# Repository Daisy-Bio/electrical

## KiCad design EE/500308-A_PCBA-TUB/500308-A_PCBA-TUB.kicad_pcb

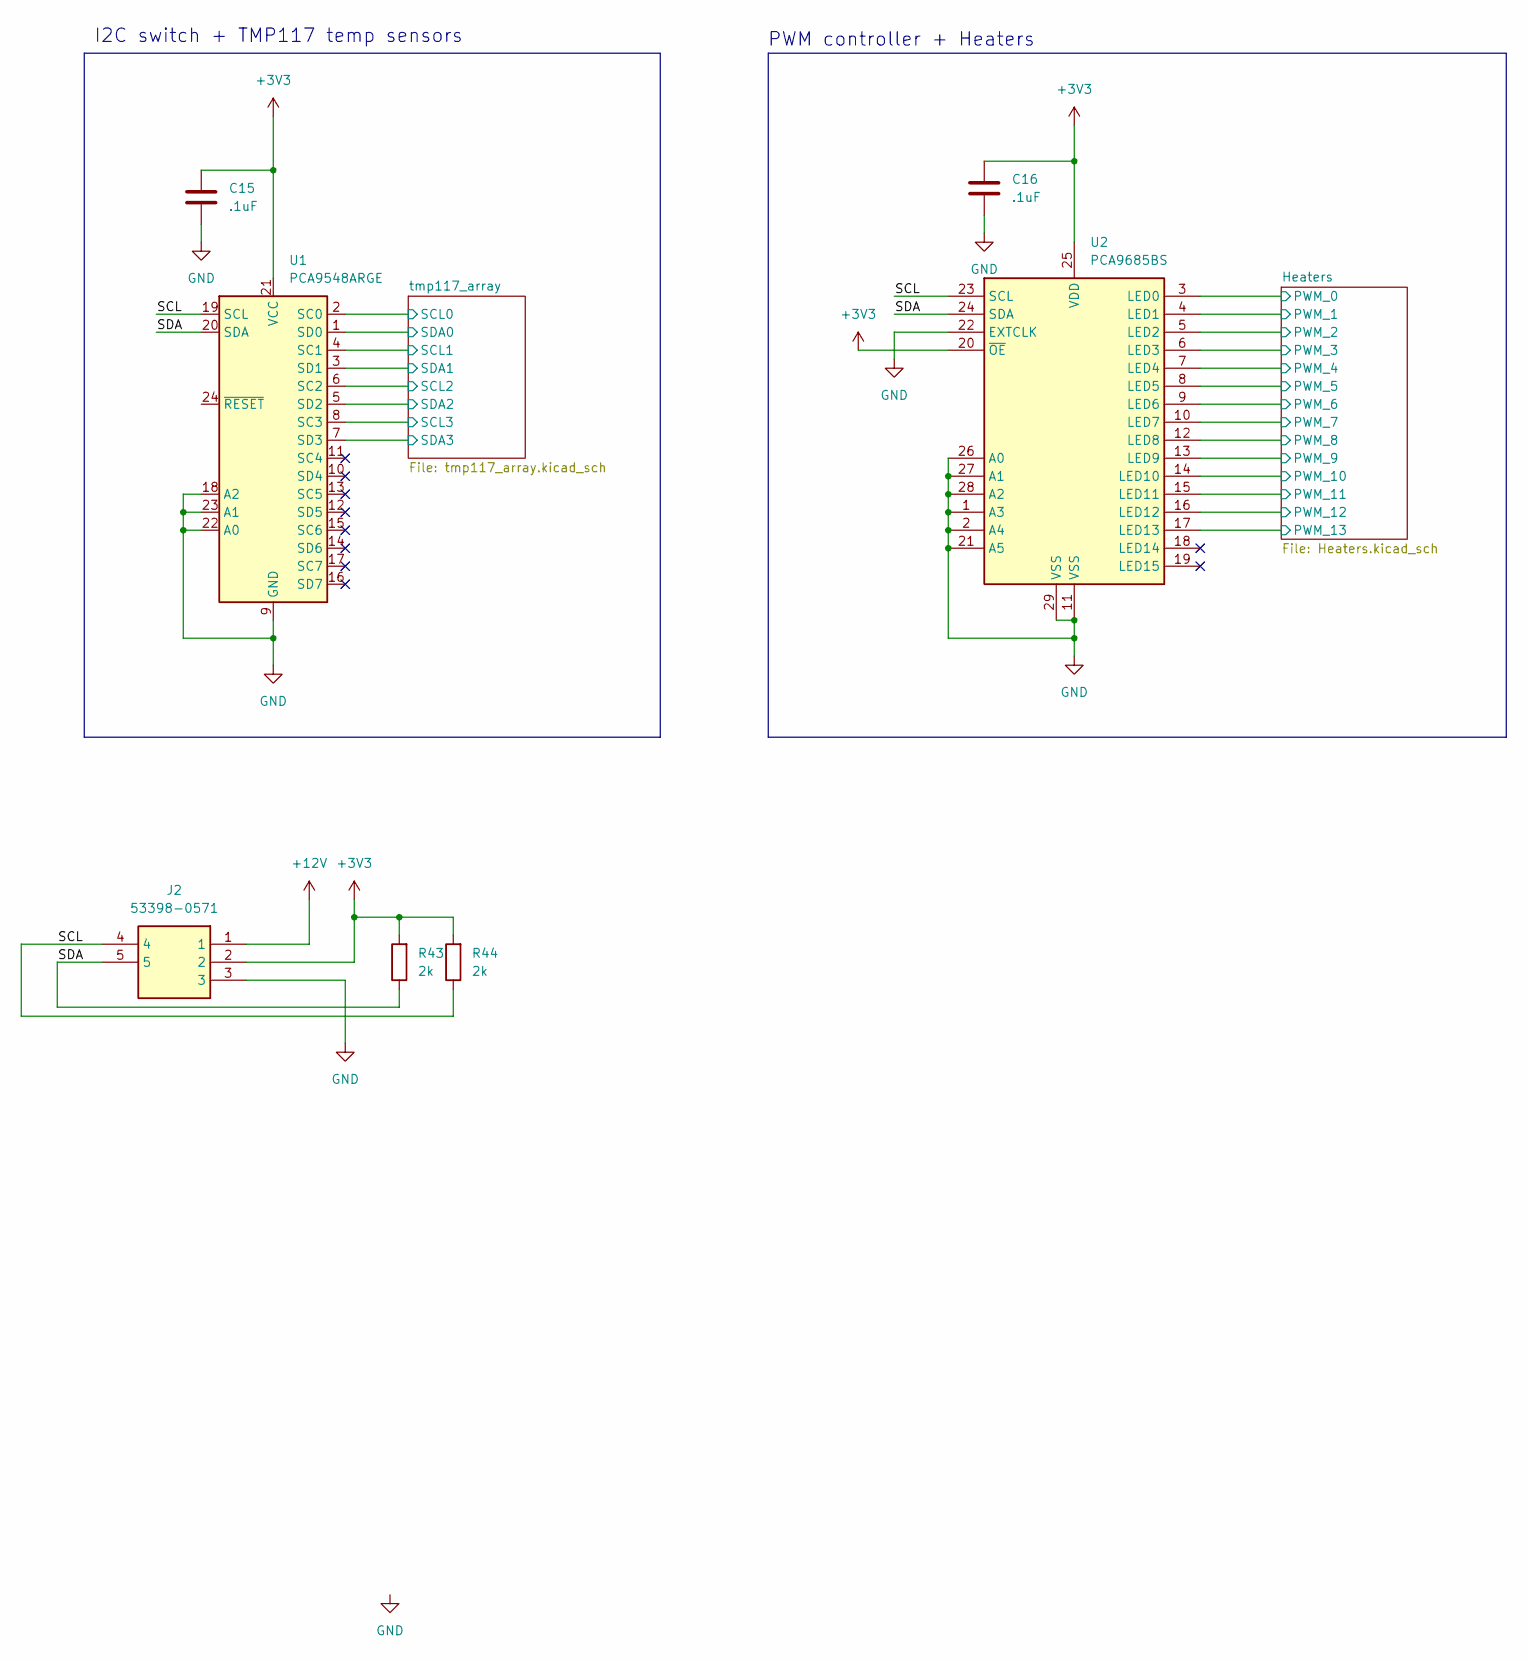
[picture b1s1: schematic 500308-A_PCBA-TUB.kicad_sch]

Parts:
C15, C16: .1uF; C_0402_1005Metric_Pad0.74x0.62mm_HandSolder
J2: 53398-0571; Mouser Part Number 538-53398-0571
R43, R44: 2k; R_0402_1005Metric
U1: PCA9548ARGE; Texas_RGE0024C_VQFN-24-1EP_4x4mm_P0.5mm_EP2.1x2.1mm
U2: PCA9685BS; QFN-28-1EP_6x6mm_P0.65mm_EP4.25x4.25mm

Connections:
+3V3: C15.1, C16.1, J2.2, R43.2, R44.2, U1.21 (VCC), U2.20 (~OE), U2.25 (VDD); also elsewhere on the board
+12V: J2.1; also elsewhere on the board
/Heaters/PWM_0: U2.3 (LED0); also elsewhere on the board
/Heaters/PWM_1: U2.4 (LED1); also elsewhere on the board
/Heaters/PWM_2: U2.5 (LED2); also elsewhere on the board
/Heaters/PWM_3: U2.6 (LED3); also elsewhere on the board
/Heaters/PWM_4: U2.7 (LED4); also elsewhere on the board
/Heaters/PWM_5: U2.8 (LED5); also elsewhere on the board
/Heaters/PWM_6: U2.9 (LED6); also elsewhere on the board
/Heaters/PWM_7: U2.10 (LED7); also elsewhere on the board
/Heaters/PWM_8: U2.12 (LED8); also elsewhere on the board
/Heaters/PWM_9: U2.13 (LED9); also elsewhere on the board
/Heaters/PWM_10: U2.14 (LED10); also elsewhere on the board
/Heaters/PWM_11: U2.15 (LED11); also elsewhere on the board
/Heaters/PWM_12: U2.16 (LED12); also elsewhere on the board
/Heaters/PWM_13: U2.17 (LED13); also elsewhere on the board
/SCL: J2.4, R44.1, U1.19 (SCL), U2.23 (SCL)
/SDA: J2.5, R43.1, U1.20 (SDA), U2.24 (SDA)
/tmp117_array/SCL0: U1.2 (SC0); also elsewhere on the board
/tmp117_array/SCL1: U1.4 (SC1); also elsewhere on the board
/tmp117_array/SCL2: U1.6 (SC2); also elsewhere on the board
/tmp117_array/SCL3: U1.8 (SC3); also elsewhere on the board
/tmp117_array/SDA0: U1.1 (SD0); also elsewhere on the board
/tmp117_array/SDA1: U1.3 (SD1); also elsewhere on the board
/tmp117_array/SDA2: U1.5 (SD2); also elsewhere on the board
/tmp117_array/SDA3: U1.7 (SD3); also elsewhere on the board
GND: C15.2, C16.2, J2.3, U1.9 (GND), U1.18 (A2), U1.22 (A0), U1.23 (A1), U2.1 (A3), U2.2 (A4), U2.11 (VSS), U2.21 (A5), U2.22 (EXTCLK), U2.26 (A0), U2.27 (A1), U2.28 (A2), U2.29 (VSS); also elsewhere on the board

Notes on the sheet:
PWM controller + Heaters
I2C switch + TMP117 temp sensors

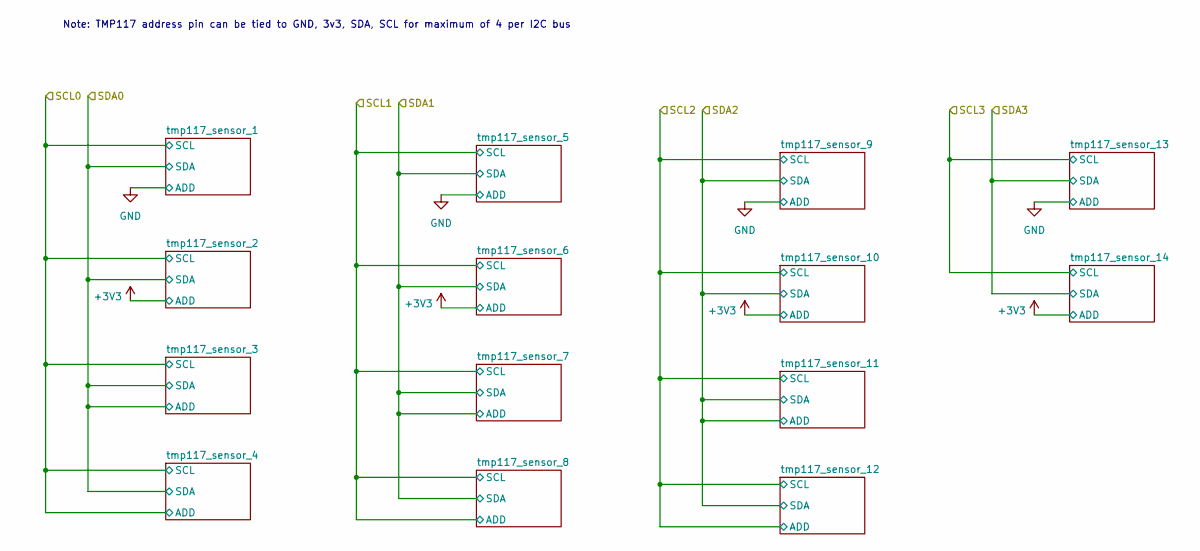
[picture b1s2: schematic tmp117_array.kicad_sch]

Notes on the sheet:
Note: TMP117 address pin can be tied to GND, 3v3, SDA, SCL for maximum of 4 per I2C bus

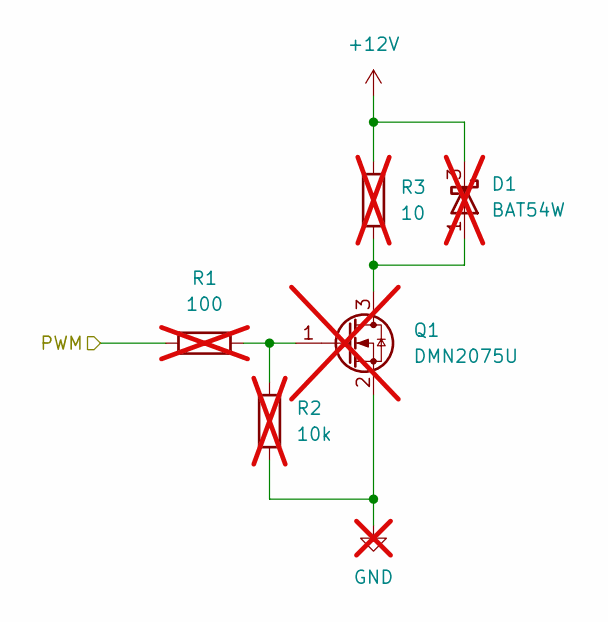
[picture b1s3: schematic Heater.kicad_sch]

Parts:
D1: BAT54W; SOT-323_SC-70; not fitted
Q1: DMN2075U; SOT-23; not fitted
R1: 100; R_0402_1005Metric; not fitted
R2: 10k; R_0402_1005Metric; not fitted
R3: 10; R_0603_1608Metric; not fitted

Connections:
+12V: D1.3 (K), R3.2; also elsewhere on the board
/Heaters/PWM_0: R1.1; also elsewhere on the board
GND: Q1.2 (S), R2.1; also elsewhere on the board
unnamed: Q1.3 (D), R3.1
unnamed: Q1.1 (G), R1.2, R2.2

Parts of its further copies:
Q2, Q3, Q4, Q5, Q6, Q7, Q8, Q9, Q10, Q11, Q12, Q13, Q14: DMN2075U; SOT-23; not fitted
R4, R7, R10, R13, R16, R19, R22, R25, R28, R31, R34, R37, R40: 100; R_0402_1005Metric; not fitted
R5, R8, R11, R14, R17, R20, R23, R26, R29, R32, R35, R38, R41: 10k; R_0402_1005Metric; not fitted
R6, R9, R12, R15, R18, R21, R24, R27, R30, R33, R36, R39, R42: 10; R_0603_1608Metric; not fitted

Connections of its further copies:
+12V: R6.2, R9.2, R12.2, R15.2, R18.2, R21.2, R24.2, R27.2, R30.2, R33.2, R36.2, R39.2, R42.2; also elsewhere on the board
/Heaters/PWM_1: R4.1; also elsewhere on the board
/Heaters/PWM_2: R7.1; also elsewhere on the board
/Heaters/PWM_3: R10.1; also elsewhere on the board
/Heaters/PWM_4: R13.1; also elsewhere on the board
/Heaters/PWM_5: R16.1; also elsewhere on the board
/Heaters/PWM_6: R19.1; also elsewhere on the board
/Heaters/PWM_7: R22.1; also elsewhere on the board
/Heaters/PWM_8: R25.1; also elsewhere on the board
/Heaters/PWM_9: R28.1; also elsewhere on the board
/Heaters/PWM_10: R31.1; also elsewhere on the board
/Heaters/PWM_11: R34.1; also elsewhere on the board
/Heaters/PWM_12: R37.1; also elsewhere on the board
/Heaters/PWM_13: R40.1; also elsewhere on the board
GND: Q2.2 (S), Q3.2 (S), Q4.2 (S), Q5.2 (S), Q6.2 (S), Q7.2 (S), Q8.2 (S), Q9.2 (S), Q10.2 (S), Q11.2 (S), Q12.2 (S), Q13.2 (S), Q14.2 (S), R5.1, R8.1, R11.1, R14.1, R17.1, R20.1, R23.1, R26.1, R29.1, R32.1, R35.1, R38.1, R41.1; also elsewhere on the board
unnamed: Q2.3 (D), R6.1
unnamed: Q2.1 (G), R4.2, R5.2
unnamed: Q3.3 (D), R9.1
unnamed: Q3.1 (G), R7.2, R8.2
unnamed: Q4.3 (D), R12.1
unnamed: Q4.1 (G), R10.2, R11.2
unnamed: Q5.3 (D), R15.1
unnamed: Q5.1 (G), R13.2, R14.2
unnamed: Q6.3 (D), R18.1
unnamed: Q6.1 (G), R16.2, R17.2
unnamed: Q7.3 (D), R21.1
unnamed: Q7.1 (G), R19.2, R20.2
unnamed: Q8.3 (D), R24.1
unnamed: Q8.1 (G), R22.2, R23.2
unnamed: Q9.3 (D), R27.1
unnamed: Q9.1 (G), R25.2, R26.2
unnamed: Q10.3 (D), R30.1
unnamed: Q10.1 (G), R28.2, R29.2
unnamed: Q11.3 (D), R33.1
unnamed: Q11.1 (G), R31.2, R32.2
unnamed: Q12.3 (D), R36.1
unnamed: Q12.1 (G), R34.2, R35.2
unnamed: Q13.3 (D), R39.1
unnamed: Q13.1 (G), R37.2, R38.2
unnamed: Q14.3 (D), R42.1
unnamed: Q14.1 (G), R40.2, R41.2

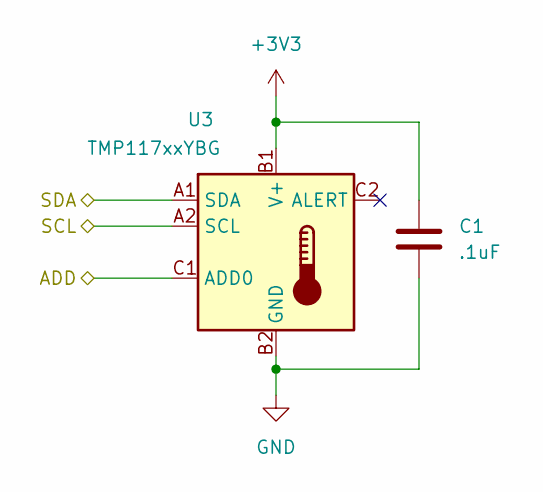
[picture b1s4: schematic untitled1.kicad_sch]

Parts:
C1: .1uF; C_0402_1005Metric_Pad0.74x0.62mm_HandSolder
U3: TMP117xxYBG; Texas_DSBGA-6_0.95x1.488mm_Layout2x3_P0.4mm

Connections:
+3V3: C1.1, U3.B1 (V+); also elsewhere on the board
/tmp117_array/SCL0: U3.A2 (SCL); also elsewhere on the board
/tmp117_array/SDA0: U3.A1 (SDA); also elsewhere on the board
GND: C1.2, U3.B2 (GND), U3.C1 (ADD0); also elsewhere on the board

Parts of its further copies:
C2, C3, C4, C5, C6, C7, C8, C9, C10, C11, C12, C13, C14: .1uF; C_0402_1005Metric_Pad0.74x0.62mm_HandSolder
U4, U5, U6, U7, U8, U9, U10, U11, U12, U13, U14, U15, U16: TMP117xxYBG; Texas_DSBGA-6_0.95x1.488mm_Layout2x3_P0.4mm

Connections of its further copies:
+3V3: C2.1, C3.1, C4.1, C5.1, C6.1, C7.1, C8.1, C9.1, C10.1, C11.1, C12.1, C13.1, C14.1, U4.B1 (V+), U4.C1 (ADD0), U5.B1 (V+), U6.B1 (V+), U7.B1 (V+), U8.B1 (V+), U8.C1 (ADD0), U9.B1 (V+), U10.B1 (V+), U11.B1 (V+), U12.B1 (V+), U12.C1 (ADD0), U13.B1 (V+), U14.B1 (V+), U15.B1 (V+), U16.B1 (V+), U16.C1 (ADD0); also elsewhere on the board
/tmp117_array/SCL0: U4.A2 (SCL), U5.A2 (SCL), U6.A2 (SCL), U6.C1 (ADD0); also elsewhere on the board
/tmp117_array/SCL1: U7.A2 (SCL), U8.A2 (SCL), U9.A2 (SCL), U10.A2 (SCL), U10.C1 (ADD0); also elsewhere on the board
/tmp117_array/SCL2: U11.A2 (SCL), U12.A2 (SCL), U13.A2 (SCL), U14.A2 (SCL), U14.C1 (ADD0); also elsewhere on the board
/tmp117_array/SCL3: U15.A2 (SCL), U16.A2 (SCL); also elsewhere on the board
/tmp117_array/SDA0: U4.A1 (SDA), U5.A1 (SDA), U5.C1 (ADD0), U6.A1 (SDA); also elsewhere on the board
/tmp117_array/SDA1: U7.A1 (SDA), U8.A1 (SDA), U9.A1 (SDA), U9.C1 (ADD0), U10.A1 (SDA); also elsewhere on the board
/tmp117_array/SDA2: U11.A1 (SDA), U12.A1 (SDA), U13.A1 (SDA), U13.C1 (ADD0), U14.A1 (SDA); also elsewhere on the board
/tmp117_array/SDA3: U15.A1 (SDA), U16.A1 (SDA); also elsewhere on the board
GND: C2.2, C3.2, C4.2, C5.2, C6.2, C7.2, C8.2, C9.2, C10.2, C11.2, C12.2, C13.2, C14.2, U4.B2 (GND), U5.B2 (GND), U6.B2 (GND), U7.B2 (GND), U7.C1 (ADD0), U8.B2 (GND), U9.B2 (GND), U10.B2 (GND), U11.B2 (GND), U11.C1 (ADD0), U12.B2 (GND), U13.B2 (GND), U14.B2 (GND), U15.B2 (GND), U15.C1 (ADD0), U16.B2 (GND); also elsewhere on the board

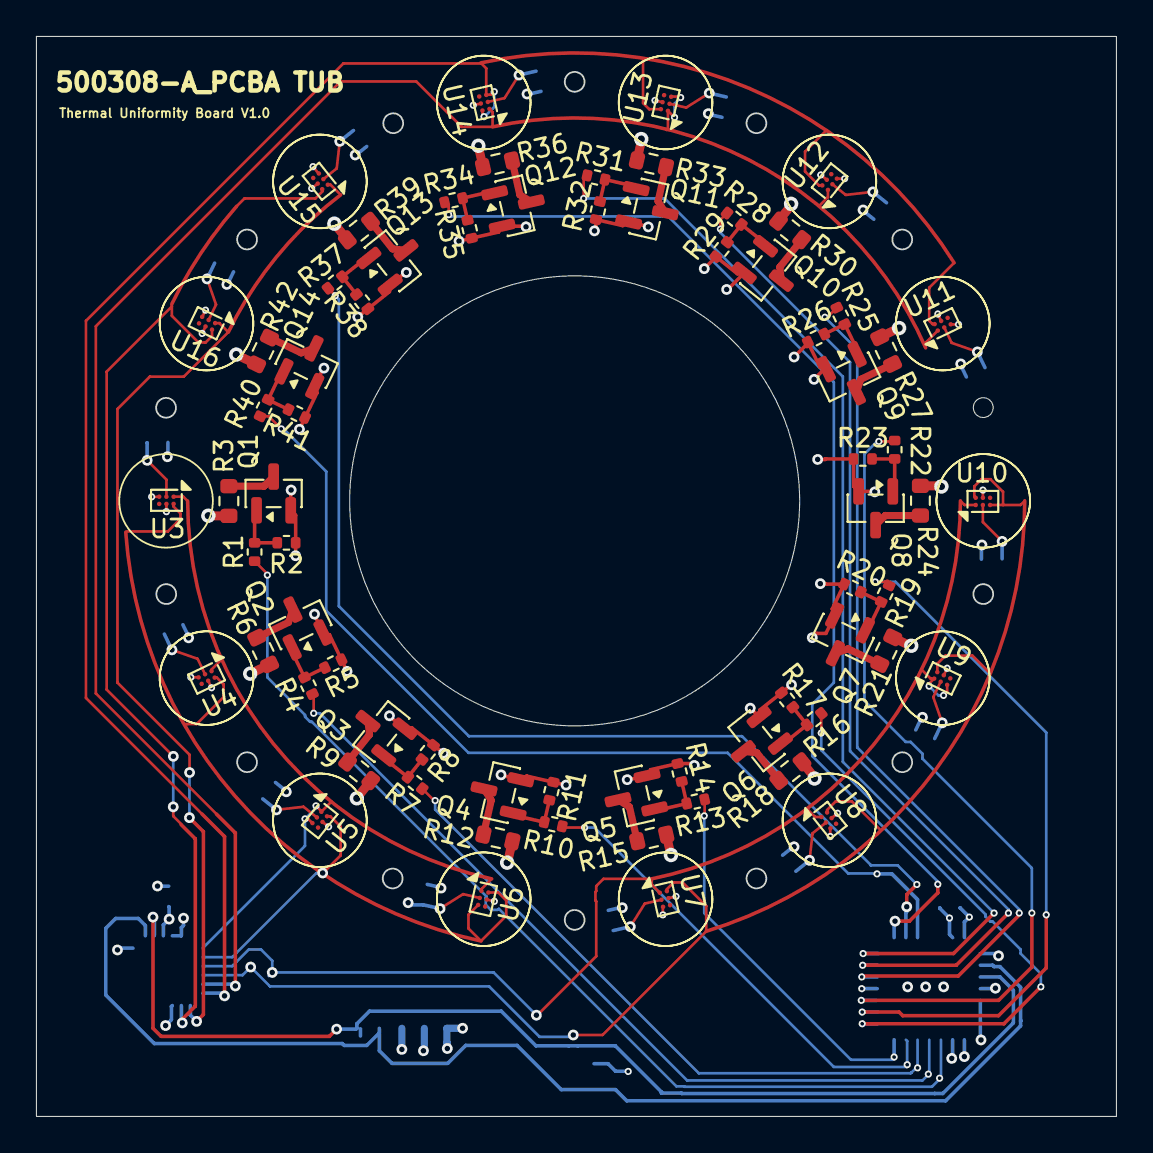
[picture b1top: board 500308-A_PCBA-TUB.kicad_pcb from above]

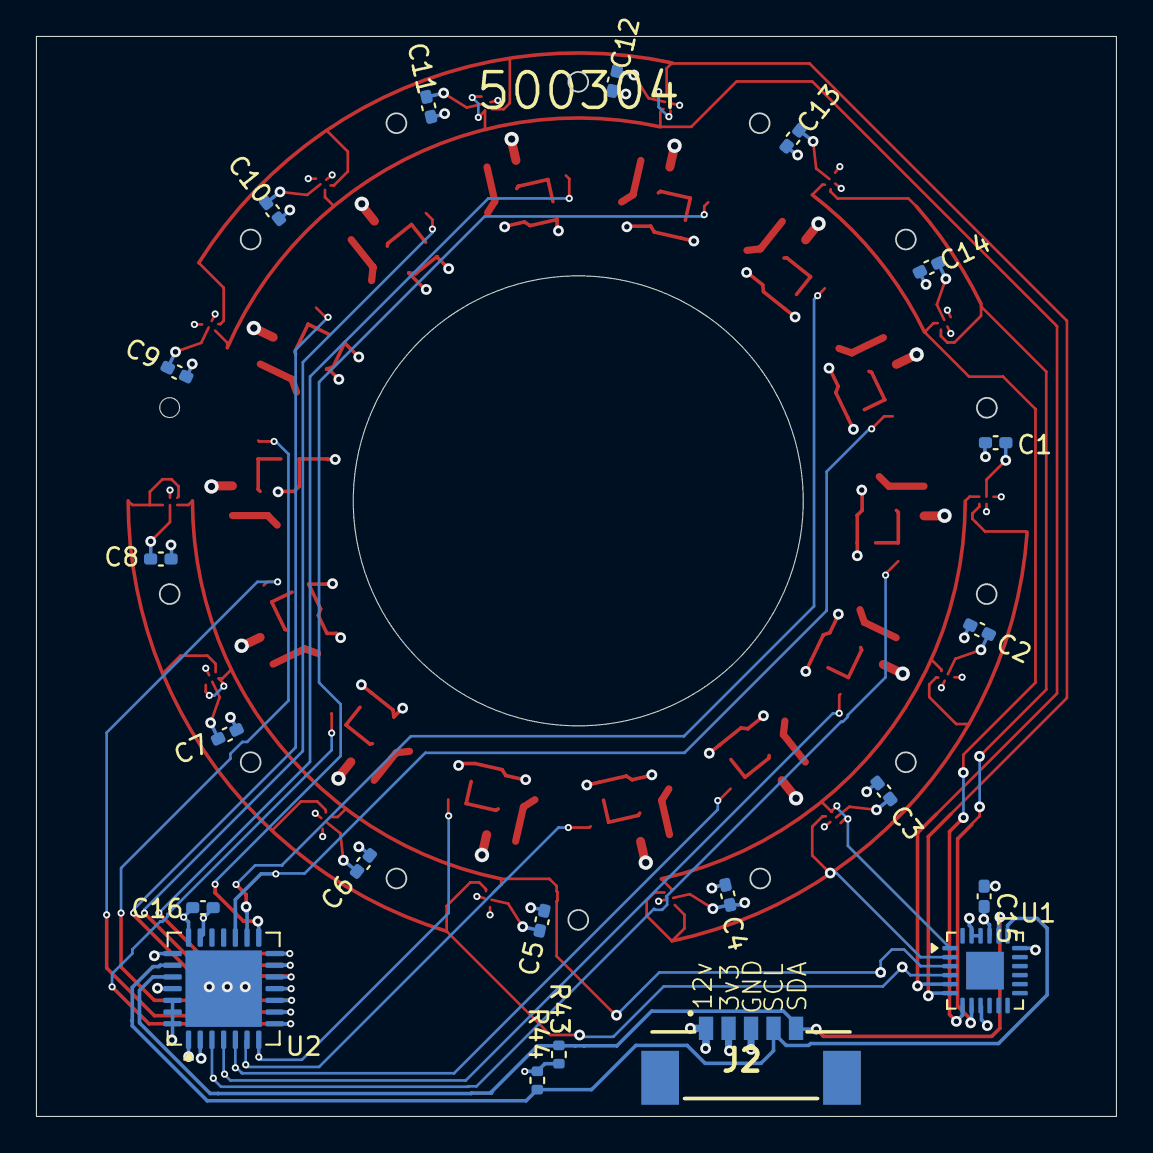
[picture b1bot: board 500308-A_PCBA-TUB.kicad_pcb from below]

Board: 4 copper layers, 59.9 x 60.0 mm, 91 parts (21 on the bottom side), 55 nets.

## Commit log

2026-01-25 Initial commit from setup script
2026-01-26 docs: use markdown license file
2026-01-29 added everything from EE folder in mira repo
    from old "mira" repo
2026-03-16 Initial design for thermal uniformity test fixture with bonus prototype heaters for fun.
2026-03-19 added step file with the board
2026-03-19 Only tmp sensors on well side
